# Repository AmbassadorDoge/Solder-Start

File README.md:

# Solder-Start

### Description

A USB powered breadboard and 1-bit memory! It also acts as a 5v power supply. I hope to inspire others to learn to solder with this.

### To Make

I will buy from JLCPCB. If you are also getting from a PCB manufacturer, use the following tips:
- Use ENIG and Gold fingers(has USB-A PCB edge!)
- When it arrives, put something ~0.5mm on the bottom of the USB part of the PCB to make sure it fits nicely onto any port.

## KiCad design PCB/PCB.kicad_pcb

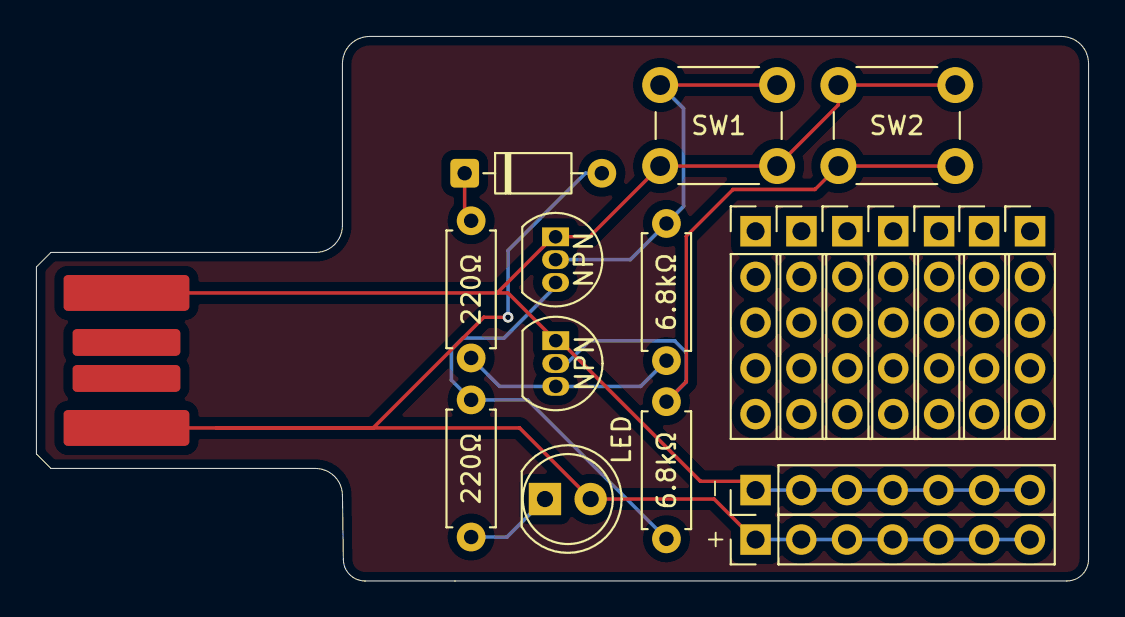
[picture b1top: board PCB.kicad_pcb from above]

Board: 2 copper layers, 58.4 x 30.2 mm, 20 parts (0 on the bottom side), 8 nets.

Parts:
6.8kΩ, 6.8kΩ#2: 6.8k; R_Axial_DIN0207_L6.3mm_D2.5mm_P7.62mm_Horizontal
220Ω, 220Ω#2: 200; R_Axial_DIN0207_L6.3mm_D2.5mm_P7.62mm_Horizontal
D2: 1N4148; D_DO-35_SOD27_P7.62mm_Horizontal
J1, J12: Conn_01x07_Pin; PinHeader_1x07_P2.54mm_Vertical
J9, J10, J13, J14, J15, J16, J17: Conn_01x05_Pin; PinHeader_1x05_P2.54mm_Vertical
J11: USB_A_PCB_Edge_receptacle
LED: LED; LED_D5.0mm
NPN: PN2222A; TO-92_Inline
NPN#2: PN2222A; TO-92_Inline
SW1, SW2: SW_Push; SW_PUSH_6mm

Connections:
+5V: D2.2 (A), J1.1, J1.2, J1.3, J1.4, J1.5, J1.6, J1.7, J11.1 (VBUS), LED.2 (A)
GND: J11.4 (GND), J12.1, J12.2, J12.3, J12.4, J12.5, J12.6, J12.7, NPN.1 (E), NPN#2.1 (E), SW1.2, SW2.1
unnamed: 220Ω#2.1, LED.1 (K)
unnamed: 220Ω.1, D2.1 (K)
unnamed: 6.8kΩ#2.2, NPN.2 (B), SW1.1
unnamed: 6.8kΩ.1, 220Ω#2.2, NPN.3 (C)
unnamed: 6.8kΩ.2, NPN#2.2 (B), SW2.2
unnamed: 6.8kΩ#2.1, 220Ω.2, NPN#2.3 (C)

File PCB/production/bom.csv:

Designator,Footprint,Quantity,Value,LCSC Part #
"220Ω_2, 220Ω",R_Axial_DIN0207_L6.3mm_D2.5mm_P7.62mm_Horizontal,2,200,
"6.8KΩ_2, 6.8KΩ",R_Axial_DIN0207_L6.3mm_D2.5mm_P7.62mm_Horizontal,2,6.8k,
D2,D_DO-35_SOD27_P7.62mm_Horizontal,1,1N4148,
"J1, J12",PinHeader_1x07_P2.54mm_Vertical,2,Conn_01x07_Pin,
"J10, J13, J14, J15, J16, J17, J9",PinHeader_1x05_P2.54mm_Vertical,7,Conn_01x05_Pin,
J11,USB_A_PCB_Edge_receptacle,1,USB_A_PCB_Edge_receptacle,
LED,LED_D5.0mm,1,LED,
"NPN_2, NPN",TO-92_Inline,2,PN2222A,
"SW1, SW2",SW_PUSH_6mm,2,SW_Push,

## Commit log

2025-10-05 Finished PCB
2025-10-05 add BOM
2025-10-05 Add .wrl
2025-10-05 Rename BOM.csv to bom.csv
2025-10-05 Added unsaved changes
2025-10-06 pcb spacing update
